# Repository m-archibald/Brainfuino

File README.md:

# Brainfuino [-]+.

```text
  ____            _        __       _           
 | __ ) _ __ __ _(_)_ __  / _|_   _(_)_ __   ___  
 |  _ \| '__/ _` | | '_ \| |_| | | | | '_ \ / _ \ 
 | |_) | | | (_| | | | | |  _| |_| | | | | | (_) |
 |____/|_|  \__,_|_|_| |_|_|  \__,_|_|_| |_|\___/ 
```

**An Arduino-like development board that executes raw Brainfuck natively in silicon.**

> ### 📖 [Read the Full Documentation](https://m-archibald.github.io/Brainfuino/)
>
> Comprehensive guides covering quick start, hardware architecture, FPGA toolchain, DirtyJTAG / Diamond flashing, STM32 firmware, 3D printing, and Brainfuck programming are live at **[https://m-archibald.github.io/Brainfuino/](https://m-archibald.github.io/Brainfuino/)**!

---

## What is Brainfuino?

You may have seen the Brainfuino [Hackaday project](https://hackaday.com/2021/01/12/make-room-for-a-new-arduino-competitor-with-native-brainfck/) released during COVID in 2021. Originally created by Eduardo Corpeño, it's a programming board that runs the esoteric programming language Brainfuck completely in hardware. The language is extremely minimal, with just 8 characters, yet it is entirely Turing complete. When uploading code to the Brainfuino, there is no conversion or compression, the ascii brainfuck characters are saved into rom exactly as they are written. Programming in Brainfuck is difficult, hilarious, and rewarding, and doing it with Brainfuino is even better.

---

## Two Processors: Pure Hardware and Quality of Life

There are two processors on the Brainfuino, the actual Brainfuck based soft processor implemented in hardware on the Lattice FPGA, and the STM32 which makes the whole thing user "friendly". Since the FPGA is configured basically as an old fashioned Harvard CPU, instructions move through the soft processor in a continuous stream of parallel bits, these flash into and out of existence, and the STM32 is there to catch them and serialize them so you can use it with a modern PC instead of an ancient parallel based terminal interface. The FPGA does all the hard work here though. When programs are run, all the output is being generated real time in hardware via the FPGA. The FPGA reads bytes of data from good old parallel flash program memory, and when it encounters bytes representing one of the 8 ascii characters used in Brainfuck it executes that with its built in soft processor based instruction set according to the character. Since it's a harvard style cpu, it also uses parallel based RAM to read and write data to and from for computation purposes. The STM32 uses its hardware timer to drive a clock pin to the FPGA at speeds from 500 khz up to 12 mhz. You may wonder if the STM32 is overkill, and your curiosity is valid, it probably is overkill, but by leveraging a separate microcontroller for these quality of life improvements, it allows the Brainfuck soft processor implemented in Verilog on the Lattice FPGA to remain pure and stay true to its purpose to compute Brainfuck. We leave the rest to the STM32: Usb communication, parallel to serial conversion, program memory flushing and prep, variable clock speed control, and an interactive terminal interface.

---

## Why Brainfuino?

As to answer the question of why? Well: The challenge. And to quote the original author Eduardo Corpeño, with the Brainfuino you get "bragging rights for writing code that works! You certainly won't get that from the Arduino."

---

## What's in Revision 1.1

My revision 1.1 of the Brainfuino has:
- Improved clock routing to the FPGA soft processor using an FPGA pin optimized for clock input rather than a generic GPIO
- Proper VBus to 3.3v connection on the STM32 increasing STM32 clock stability
- JLCPCB compatible parts list and reduced cost by switching to prestocked "basic" components.
- USB C!
- A nifty 3D printed case
- KiCAD design files (migrated from the original Autodesk Eagle)

See the original demo video: [Brainfuino: Hardware Brainfuck Processor (YouTube)](https://www.youtube.com/watch?v=QloNq8AoHvU)

---

## Three Languages in One Project

Three different programming paradigms come together to bring Brainfuino to life:

| Language        | Layer                    | Purpose                                                                                                                              |
| :-------------- | :----------------------- | :----------------------------------------------------------------------------------------------------------------------------------- |
| **Brainfuck**   | **Application**          | The end-user language. Programs are written in standard Brainfuck and run directly on the hardware tape.                             |
| **Verilog HDL** | **Processor Core**       | Defines the`brainfuck_uP` digital architecture, instruction decoder, and state machine synthesized into the FPGA bitstream (`.jed`). |
| **Embedded C**  | **Coprocessor Firmware** | Powers the STM32F072 microcontroller, managing USB CDC communications, clock synthesis, and ROM flashing.                            |

---

## Repository Structure

This repository is the consolidated monorepo for the entire Brainfuino project:

- [`brainfuino-PCB/`](./brainfuino-PCB/): Hardware schematics and board layouts for **Rev 1.0** (Eagle) and **Rev 1.1** (KiCad with JLCPCB fabrication Gerbers, BOM, and CPL).
- [`brainfuck_uP-FPGA-softprocessor/`](./brainfuck_uP-FPGA-softprocessor/): Lattice MachXO2 soft-processor in Verilog, pin constraints (`.lpf`), and Lattice Diamond project files.
- [`companion-STM32-firmware/`](./companion-STM32-firmware/): STM32F072 firmware (STM32CubeIDE project) handling USB CDC serial, clock generation, and ROM flashing.
- [`3D-printable-case/`](./3D-printable-case/): SolidWorks (`.SLDPRT`) and 3D printing CAD models (`.STEP`) for the custom enclosure.
- [`documentation/`](./documentation/): Comprehensive MkDocs Material documentation source files and project guides.

---

## Project Origins & Acknowledgements

The Brainfuino project was originally conceived, designed, and built by **Eduardo Corpeño** ([kuashio](https://github.com/kuashio)).

- **Video Demonstration:** [Brainfuino: Hardware Brainfuck Processor (YouTube)](https://youtu.be/QloNq8AoHvU)
- **Project Build Log:** [Brainfuino on Hackaday.io](https://hackaday.io/project/176757-brainfuino)
- **Original Soft-Processor:** [kuashio/brainfuck_uP](https://github.com/kuashio/brainfuck_up)
- **Original STM32 Firmware:** [kuashio/brainfuino-firmware](https://github.com/kuashio/brainfuino-firmware)
- **Brainfuck IDE:** [Visual brainfuck](https://sites.google.com/site/visualbf/)

Continued and maintained by:

- **Matthew Archibald:** Hardware modernization, KiCad Rev 1.1 redesign, JLCPCB manufacturing packages, 3D-printable case, and documentation.
- **Thalia Archibald:** Software architecture, compiler engineering, and curator of the [bfcorpus repository](https://github.com/thaliaarchi/bfcorpus) and [bfcoq](https://github.com/thaliaarchi/bfcoq).

---

### Ready to Build or Program?

Check out the official documentation for step-by-step assembly guides, bitstream flashing, and terminal operation:
**[https://m-archibald.github.io/Brainfuino/](https://m-archibald.github.io/Brainfuino/)**

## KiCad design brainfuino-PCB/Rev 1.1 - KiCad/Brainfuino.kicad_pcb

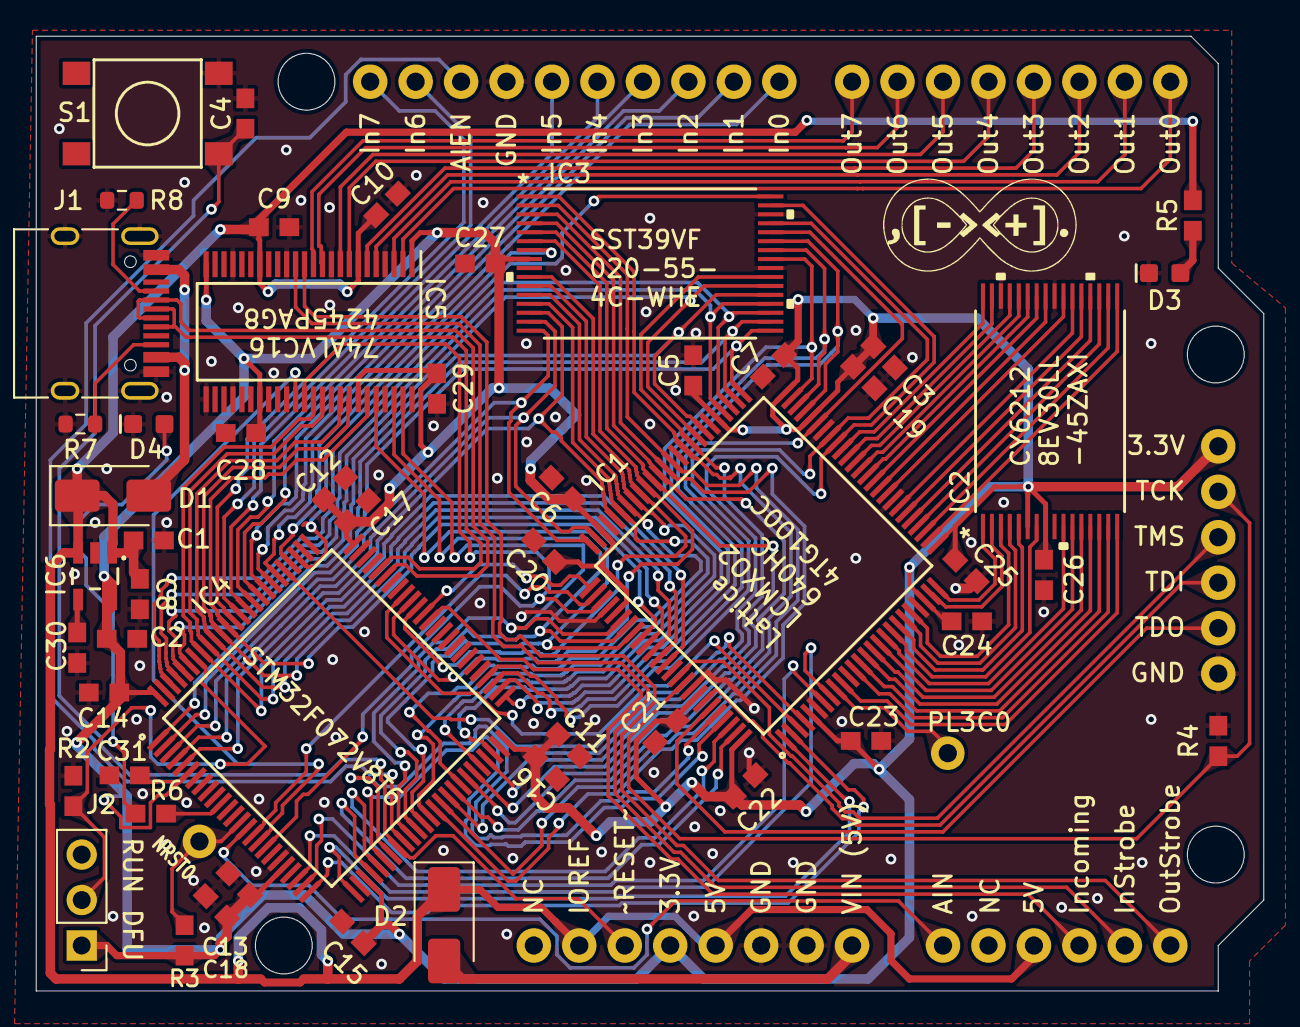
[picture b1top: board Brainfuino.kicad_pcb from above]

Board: 2 copper layers, 68.6 x 53.3 mm, 54 parts (0 on the bottom side), 119 nets.

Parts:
B1: ARDUINO_UNO_R3; ARDUINO_R3
C1: 10uF; 0603
C2, C8, C13: 1.0uF; 0603
C3, C4, C9, C10, C14, C15, C16, C17, C26, C27, C28, C29, C31: 0.1uF; 0603
C5, C6, C7, C18, C19, C20, C21, C22, C23, C24, C25, C30: 10nF; 0603
C11, C12: 4.7uF; 0603
D1, D2: SS12; D_SMA
D3: GREEN; LED-0603
D4: RED; LED-0603
IC1: LCMXO2-640HC-4TG100C; QFP50P1600X1600X160-100N
IC2: CY62128EV30LL-45AXI; TSOP-32
IC3: SST39LF020-55-4C-WHE; TSOP32_WH_SST
IC4: STM32F072V8T6; QFP50P1600X1600X160-100N
IC5: 74ALVC164245PAG8; SOP50P810X120-48N
IC6: SPX3819M5_3_3; SOT23-5
J1: USB_C_Receptacle_USB2.0_16P; USB_C_Receptacle_HRO_TYPE-C-31-M-12
J2: Conn_01x03_Pin; PinHeader_1x03_P2.54mm_Vertical
NRST0: TEST-POINTPOGO_PTH; 1X01_NO_SILK
PL3C0: TEST-POINTPOGO_PTH; 1X01_NO_SILK
R2: 22k; 0603
R3: 100k; 0603
R4, R5: 4.7k; 0603
R6: 680; 0603
R7, R8: 5.1k; R_0603_1608Metric
S1: RESET; TACTILE_SWITCH_SMD_6.2MM_TALL

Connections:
3.3V: B1.3.3V, B1.VCC, C2.1, C3.1, C5.1, C6.1, C7.1, C11.1, C12.1, C13.1, C14.1, C15.1, C16.1, C17.1, C18.1, C19.1, C20.1, C21.1, C22.1, C23.1, C24.1, C25.1, C26.1, C27.1, C28.1, C29.1, C31.2, IC1.5 (VCCIO3_1), IC1.23 (VCCIO3_2), IC1.26 (VCCIO2_1), IC1.46 (VCCIO2_2), IC1.50 (VCC_1), IC1.55 (VCCIO1_1), IC1.73 (VCCIO1_2), IC1.80 (VCCIO0_1), IC1.93 (VCCIO0_2), IC1.100 (VCC_2), IC2.6 (CE2), IC2.8 (VCC), IC3.8 (VDD), IC4.6 (VBAT), IC4.21 (VDDA), IC4.28 (VDD_1), IC4.50 (VDD_2), IC4.75 (VDDIO2), IC4.100 (VDD_3), IC5.1 (1DIR), IC5.24 (2DIR), IC5.31 (VCCA_(3.3V)_1), IC5.42 (VCCA_(3.3V)_2), IC6.5 (OUT), J2.1, R3.1
5V: B1.5V, B1.5V@1, B1.IOREF, C1.1, C8.1, C9.1, C10.1, D1.1 (K), D2.1 (K), IC5.7 ((5V)_VCCB_1), IC5.18 ((5V)_VCCB_2), IC6.1 (IN), IC6.3 (EN), R5.2
/A0: IC1.54 (PR7A), IC3.20 (A0), IC4.97 (PE0)
/A1: IC1.53 (PR7B), IC3.19 (A1), IC4.98 (PE1)
/A2: IC1.52 (PR7C), IC3.18 (A2), IC4.1 (PE2)
/A3: IC1.51 (PR7D), IC3.17 (A3), IC4.2 (PE3)
/A4: IC1.75 (PR2A), IC3.16 (A4), IC4.3 (PE4)
/A5: IC1.74 (PR2B), IC3.15 (A5), IC4.4 (PE5)
/A6: IC1.71 (PR2C), IC3.14 (A6), IC4.5 (PE6)
/A7: IC1.70 (PR2D), IC3.13 (A7), IC4.38 (PE7)
/A8: IC1.63 (PR5C), IC3.3 (A8), IC4.39 (PE8)
/A9: IC1.62 (PR5D), IC3.2 (A9), IC4.40 (PE9)
/A10: IC1.42 (PB12C), IC3.31 (A10), IC4.41 (PE10)
/A11: IC1.60 (PR6A), IC3.1 (A11), IC4.42 (PE11)
/A12: IC1.69 (PR3A), IC3.12 (A12), IC4.43 (PE12)
/A13: IC1.64 (PR5B), IC3.4 (A13), IC4.44 (PE13)
/A14: IC1.65 (PR5A), IC3.5 (A14), IC4.45 (PE14)
/A15: IC1.68 (PR3B), IC3.11 (A15), IC4.46 (PE15)
/A16: IC1.67 (PR3C), IC3.10 (A16), IC4.65 (PC8)
/A17: IC1.66 (PR3D), IC3.6 (A17), IC4.66 (PC9)
/AIEN: B1.AREF (AIEN), IC4.34 (PC5)
/AIN0: B1.AIN, IC4.15 (PC0)
/BF_CLK: IC1.3 (PL2C), IC4.67 (PA8)
/BF_RST: IC1.4 (PL2D), IC4.80 (PC12)
/BOOT0: IC4.94 (BOOT0), J2.2, R2.2
/BRD_RST: B1.RESET@1 (~RESET@1), C4.1, IC4.33 (PC4), S1.A2 (1)
/D0: IC1.57 (PR6D), IC3.21 (DQ0), IC4.95 (PB8)
/D1: IC1.58 (PR6C), IC3.22 (DQ1), IC4.96 (PB9)
/D2: IC1.59 (PR6B), IC3.23 (DQ2), IC4.47 (PB10)
/D3: IC1.49 (PB14D), IC3.25 (DQ3), IC4.48 (PB11)
/D4: IC1.48 (PB14C), IC3.26 (DQ4), IC4.51 (PB12)
/D5: IC1.47 (PB14B), IC3.27 (DQ5), IC4.52 (PB13)
/D6: IC1.45 (PB14A), IC3.28 (DQ6), IC4.53 (PB14)
/D7: IC1.43 (PB12D), IC3.29 (DQ7), IC4.54 (PB15)
/IN0: B1.IN0, IC4.81 (PD0)
/IN0_BFUP: IC1.8 (PL3B), IC4.23 (PA0)
/IN1: B1.IN1, IC4.82 (PD1)
/IN1_BFUP: IC1.7 (PL3A), IC4.24 (PA1)
/IN2: B1.IN2, IC4.83 (PD2)
/IN2_BFUP: IC1.2 (PL2B), IC4.25 (PA2)
/IN3: B1.IN3, IC4.84 (PD3)
/IN3_BFUP: IC1.1 (PL2A), IC4.26 (PA3)
/IN4: B1.IN4, IC4.85 (PD4)
/IN4_BFUP: IC1.99 (PT6A), IC4.29 (PA4)
/IN5: B1.IN5, IC4.86 (PD5)
/IN5_BFUP: IC1.98 (PT6B), IC4.30 (PA5)
/IN6: B1.IN6, IC4.87 (PD6)
/IN6_BFUP: IC1.97 (PT6C), IC4.31 (PA6)
/IN7: B1.IN7, IC4.88 (PD7)
/IN7_BFUP: IC1.96 (PT6D), IC4.32 (PA7)
/INCMG: B1.INCOMING, IC4.63 (PC6)
/INCMG_BFUP: IC1.76 (PT11D), IC4.64 (PC7)
/INSTRB: B1.INST (INSTRB), IC5.14 (2B2)
/INSTR_BFUP: IC1.77 (PT11C), IC4.16 (PC1)
/INSTR_LVL: IC4.17 (PC2), IC5.35 (2A2)
/OE: IC3.32 (~OE), IC4.78 (PC10)
/OUT0: IC1.81 (PT10D), IC4.35 (PB0), IC5.47 (1A1)
/OUT1: IC1.82 (PT10C), IC4.36 (PB1), IC5.46 (1A2)
/OUT2: IC1.83 (PT10B), IC4.37 (PB2), IC5.44 (1A3)
/OUT3: IC1.84 (PT10A), IC4.89 (PB3), IC5.43 (1A4)
/OUT4: IC1.85 (PT9D), IC4.90 (PB4), IC5.41 (1A5)
/OUT5: IC1.86 (PT9C), IC4.91 (PB5), IC5.40 (1A6)
/OUT6: IC1.87 (PT9B), IC4.92 (PB6), IC5.38 (1A7)
/OUT7: IC1.88 (PT9A), IC4.93 (PB7), IC5.37 (1A8)
/OUTSTRB: B1.OUTST (OUTSTRB), IC5.13 (2B1)
/OUTSTR_BFUP: IC1.78 (PT11A), IC4.18 (PC3), IC5.36 (2A1)
/TCK: B1.TCK, IC1.91 (PT7C), R4.2
/TDI: B1.TDI, IC1.94 (PT7B)
/TDO: B1.TDO, IC1.95 (PT7A)
/TMS: B1.TMS, IC1.90 (PT7D)
/USB_DN: IC4.70 (PA11), J1.A7 (D-), J1.B7 (D-)
/USB_DP: IC4.71 (PA12), J1.A6 (D+), J1.B6 (D+)
/WE: IC3.7 (~WE), IC4.79 (PC11)
GND: B1.GND@1 (GND), B1.GND@2 (GND@0), B1.GND@3 (GND@1), B1.GND@4 (GND@2), C1.2, C2.2, C3.2, C4.2, C5.2, C6.2, C7.2, C8.2, C9.2, C10.2, C11.2, C12.2, C13.2, C14.2, C15.2, C16.2, C17.2, C18.2, C19.2, C20.2, C21.2, C22.2, C23.2, C24.2, C25.2, C26.2, C27.2, C28.2, C29.2, C30.2, C31.1, D3.C, D4.C, IC1.6 (GND_1), IC1.22 (GND_2), IC1.33 (GND_3), IC1.44 (GND_4), IC1.56 (GND_5), IC1.72 (GND_6), IC1.79 (GND_7), IC1.92 (GND_8), IC2.24 (GND), IC2.30 (~CE1), IC3.24 (VSS), IC3.30 (~CE), IC4.20 (VSSA), IC4.27 (VSS_1), IC4.49 (VSS_2), IC4.74 (VSS_3), IC4.99 (VSS_4), IC5.4 (GND_1), IC5.10 (GND_2), IC5.15 (GND_3), IC5.21 (GND_4), IC5.25 (2~OE), IC5.28 (GND_5), IC5.34 (GND_6), IC5.39 (GND_7), IC5.45 (GND_8), IC5.48 (1~OE), IC6.2 (GND), J1.A1 (GND), J1.A12 (GND), J1.B1 (GND), J1.B12 (GND), J1.S1 (SHIELD), R2.1, R4.1, R7.2, R8.2, S1.B2 (2)
unnamed: D1.2 (A), J1.A4 (VBUS), J1.A9 (VBUS), J1.B4 (VBUS), J1.B9 (VBUS)
unnamed: B1.VIN, D2.2 (A)
unnamed: D3.A, R5.1
unnamed: D4.A, R6.1
unnamed: IC1.27 (PB4A), IC2.17 (A3)
unnamed: IC1.28 (PB4B), IC2.18 (A2)
unnamed: IC1.29 (PB4C), IC2.19 (A1)
unnamed: IC1.30 (PB4D), IC2.20 (A0)
unnamed: IC1.31 (PB6A), IC2.21 (I/O0)
unnamed: IC1.32 (PB6B), IC2.22 (I/O1)
unnamed: IC1.34 (PB6C), IC2.23 (I/O2)
unnamed: IC1.35 (PB6D), IC2.25 (I/O3)
unnamed: IC1.36 (PB10A), IC2.26 (I/O4)
unnamed: IC1.37 (PB10B), IC2.27 (I/O5)
unnamed: IC1.38 (PB10C), IC2.28 (I/O6)
unnamed: IC1.39 (PB10D), IC2.29 (I/O7)
unnamed: IC1.40 (PB12A), IC2.31 (A10)
unnamed: IC1.41 (PB12B), IC2.32 (~OE)
unnamed: IC1.9 (PL3C), PL3C0.1
unnamed: IC1.10 (PL3D), IC2.16 (A4)
unnamed: IC1.12 (PL5A), IC2.15 (A5)
unnamed: IC1.13 (PL5B), IC2.14 (A6)
unnamed: IC1.14 (PL5C), IC2.13 (A7)
unnamed: IC1.15 (PL5D), IC2.12 (A12)
unnamed: IC1.16 (PL6A), IC2.11 (A14)
unnamed: IC1.17 (PL6B), IC2.10 (A16)
unnamed: IC1.18 (PL6C), IC2.7 (A15)
unnamed: IC1.19 (PL6D), IC2.5 (~WE)
unnamed: IC1.20 (PL7A), IC2.4 (A13)
unnamed: IC1.21 (PL7B), IC2.3 (A8)
unnamed: IC1.24 (PL7C), IC2.2 (A9)
unnamed: IC1.25 (PL7D), IC2.1 (A11)
unnamed: IC4.14 (NRST), NRST0.1, R3.2
unnamed: IC4.11 (PF10), R6.2
unnamed: B1.OUT0, IC5.2 (1B1)
unnamed: B1.OUT1, IC5.3 (1B2)
unnamed: B1.OUT2, IC5.5 (1B3)
unnamed: B1.OUT3, IC5.6 (1B4)
unnamed: B1.OUT4, IC5.8 (1B5)
unnamed: B1.OUT5, IC5.9 (1B6)
unnamed: B1.OUT6, IC5.11 (1B7)
unnamed: B1.OUT7, IC5.12 (1B8)
unnamed: C30.1, IC6.4 (BP)
unnamed: J1.A5 (CC1), R8.1
unnamed: J1.B5 (CC2), R7.1

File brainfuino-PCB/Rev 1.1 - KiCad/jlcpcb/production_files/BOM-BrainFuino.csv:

Comment,Designator,Footprint,LCSC,Quantity
0.1uF,"C10,C14,C15,C16,C17,C26,C27,C28,C29,C3,C31,C4,C9",0603,C14663,13
1.0uF,"C13,C2,C8",0603,C15849,3
100k,R3,0603,C25803,1
10nF,"C18,C19,C20,C21,C22,C23,C24,C25,C30,C5,C6,C7",0603,C57112,12
10uF,C1,0603,C19702,1
22k,R2,0603,C31850,1
4.7k,"R4,R5",0603,C23162,2
4.7uF,"C11,C12",0603,C19666,2
5.1k,"R7,R8",R_0603_1608Metric,C23186,2
680,R6,0603,C23212,1
74ALVC164245PAG8,IC5,SOP50P810X120-48N,C2677360,1
CY62128EV30LL-45AXI,IC2,TSOP-32,C2944685,1
GREEN,D3,LED-0603,C2290,1
LCMXO2-640HC-4TG100C,IC1,QFP50P1600X1600X160-100N,C1519051,1
RED,D4,LED-0603,C2286,1
RESET,S1,TACTILE_SWITCH_SMD_6.2MM_TALL,C2909692,1
SPX3819M5_3_3,IC6,SOT23-5,C9055,1
SS12,"D1,D2",D_SMA,C2480,2
SST39LF020-55-4C-WHE,IC3,TSOP32_WH_SST,C630573,1
STM32F072V8T6,IC4,QFP50P1600X1600X160-100N,C125825,1
USB_C_Receptacle_USB2.0_16P,J1,USB_C_Receptacle_HRO_TYPE-C-31-M-12,C165948,1

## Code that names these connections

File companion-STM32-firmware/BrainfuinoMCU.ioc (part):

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Mcu.Name=STM32F072V(8-B)Tx
Mcu.Package=LQFP100
Mcu.UserName=STM32F072V8Tx
PA0.GPIOParameters=GPIO_Speed,PinState,GPIO_PuPd,GPIO_Label,GPIO_ModeDefaultOutputPP
PA0.GPIO_Label=BF_IN0
PA0.GPIO_ModeDefaultOutputPP=GPIO_MODE_OUTPUT_PP
PA0.GPIO_PuPd=GPIO_NOPULL
PA0.GPIO_Speed=GPIO_SPEED_FREQ_MEDIUM
PA0.PinState=GPIO_PIN_RESET
PA0.Signal=GPIO_Output
PA1.GPIOParameters=GPIO_Speed,PinState,GPIO_PuPd,GPIO_Label,GPIO_ModeDefaultOutputPP
PA1.GPIO_Label=BF_IN1
PA1.GPIO_ModeDefaultOutputPP=GPIO_MODE_OUTPUT_PP
PA1.GPIO_PuPd=GPIO_NOPULL
PA1.GPIO_Speed=GPIO_SPEED_FREQ_MEDIUM
PA1.PinState=GPIO_PIN_RESET
PA1.Signal=GPIO_Output
PA11.Mode=Device
PA11.Signal=USB_DM
PA12.Mode=Device
PA12.Signal=USB_DP
PA2.GPIOParameters=GPIO_Speed,PinState,GPIO_PuPd,GPIO_Label,GPIO_ModeDefaultOutputPP
PA2.GPIO_Label=BF_IN2
PA2.GPIO_ModeDefaultOutputPP=GPIO_MODE_OUTPUT_PP
PA2.GPIO_PuPd=GPIO_NOPULL
PA2.GPIO_Speed=GPIO_SPEED_FREQ_MEDIUM
PA2.PinState=GPIO_PIN_RESET
PA2.Signal=GPIO_Output
PA3.GPIOParameters=GPIO_Speed,GPIO_Label
PA3.GPIO_Label=BF_IN3
PA3.GPIO_Speed=GPIO_SPEED_FREQ_MEDIUM
PA3.Signal=GPIO_Output
PA4.GPIOParameters=GPIO_Speed,PinState,GPIO_PuPd,GPIO_Label,GPIO_ModeDefaultOutputPP
PA4.GPIO_Label=BF_IN4
PA4.GPIO_ModeDefaultOutputPP=GPIO_MODE_OUTPUT_PP
PA4.GPIO_PuPd=GPIO_NOPULL
PA4.GPIO_Speed=GPIO_SPEED_FREQ_MEDIUM
PA4.PinState=GPIO_PIN_RESET
PA4.Signal=GPIO_Output
PA5.GPIOParameters=GPIO_Speed,PinState,GPIO_PuPd,GPIO_Label,GPIO_ModeDefaultOutputPP
PA5.GPIO_Label=BF_IN5
PA5.GPIO_ModeDefaultOutputPP=GPIO_MODE_OUTPUT_PP
PA5.GPIO_PuPd=GPIO_NOPULL
PA5.GPIO_Speed=GPIO_SPEED_FREQ_MEDIUM
PA5.PinState=GPIO_PIN_RESET
PA5.Signal=GPIO_Output
PA6.GPIOParameters=GPIO_Speed,PinState,GPIO_PuPd,GPIO_Label,GPIO_ModeDefaultOutputPP
PA6.GPIO_Label=BF_IN6
PA6.GPIO_ModeDefaultOutputPP=GPIO_MODE_OUTPUT_PP
PA6.GPIO_PuPd=GPIO_NOPULL
PA6.GPIO_Speed=GPIO_SPEED_FREQ_MEDIUM
PA6.PinState=GPIO_PIN_RESET
PA6.Signal=GPIO_Output
PA7.GPIOParameters=GPIO_Speed,PinState,GPIO_PuPd,GPIO_Label,GPIO_ModeDefaultOutputPP
PA7.GPIO_Label=BF_IN7
PA7.GPIO_ModeDefaultOutputPP=GPIO_MODE_OUTPUT_PP
PA7.GPIO_PuPd=GPIO_NOPULL
PA7.GPIO_Speed=GPIO_SPEED_FREQ_MEDIUM
PA7.PinState=GPIO_PIN_RESET
PA7.Signal=GPIO_Output
PA8.GPIOParameters=GPIO_Speed,GPIO_Label
PA8.GPIO_Label=BF_CLK
PA8.GPIO_Speed=GPIO_SPEED_FREQ_HIGH
PA8.Mode=Clock-out
PA8.Signal=RCC_MCO
PB0.GPIOParameters=GPIO_Label
PB0.GPIO_Label=BF_OUT0
PB0.Signal=GPIO_Input
PB1.GPIOParameters=GPIO_Label
PB1.GPIO_Label=BF_OUT1
PB1.Signal=GPIO_Input
PB10.GPIOParameters=GPIO_Label
PB10.GPIO_Label=D2
PB10.Signal=GPIO_Input
PB11.GPIOParameters=GPIO_Label
PB11.GPIO_Label=D3
PB11.Signal=GPIO_Input
PB12.GPIOParameters=GPIO_Label
PB12.GPIO_Label=D4
PB12.Signal=GPIO_Input
PB13.GPIOParameters=GPIO_Label
PB13.GPIO_Label=D5
PB13.Signal=GPIO_Input
PB14.GPIOParameters=GPIO_Label
PB14.GPIO_Label=D6
PB14.Signal=GPIO_Input
PB15.GPIOParameters=GPIO_Label
PB15.GPIO_Label=D7
PB15.Signal=GPIO_Input
PB2.GPIOParameters=GPIO_Label
PB2.GPIO_Label=BF_OUT2
PB2.Signal=GPIO_Input
PB3.GPIOParameters=GPIO_Label
PB3.GPIO_Label=BF_OUT3
PB3.Signal=GPIO_Input
PB4.GPIOParameters=GPIO_Label
PB4.GPIO_Label=BF_OUT4
PB4.Signal=GPIO_Input
PB5.GPIOParameters=GPIO_Label
PB5.GPIO_Label=BF_OUT5
PB5.Signal=GPIO_Input
PB6.GPIOParameters=GPIO_Label
PB6.GPIO_Label=BF_OUT6
PB6.Signal=GPIO_Input
PB7.GPIOParameters=GPIO_Label
PB7.GPIO_Label=BF_OUT7
PB7.Signal=GPIO_Input
PB8.GPIOParameters=GPIO_Label
PB8.GPIO_Label=D0
PB8.Signal=GPIO_Input
PB9.GPIOParameters=GPIO_Label
PB9.GPIO_Label=D1
PB9.Signal=GPIO_Input
PC0.GPIOParameters=GPIO_Label
PC0.GPIO_Label=AIN0
PC0.Mode=IN10
PC0.Signal=ADC_IN10
PC1.GPIOParameters=GPIO_PuPd,GPIO_Label,GPIO_ModeDefaultEXTI
PC1.GPIO_Label=BF_INSTRB
PC1.GPIO_ModeDefaultEXTI=GPIO_MODE_IT_FALLING
PC1.GPIO_PuPd=GPIO_PULLUP
PC1.Signal=GPXTI1
PC10.GPIOParameters=GPIO_Speed,PinState,GPIO_Label
PC10.GPIO_Label=OE
PC10.GPIO_Speed=GPIO_SPEED_FREQ_MEDIUM
PC10.PinState=GPIO_PIN_SET
PC10.Signal=GPIO_Output
PC11.GPIOParameters=GPIO_Speed,PinState,GPIO_Label
PC11.GPIO_Label=WE
PC11.GPIO_Speed=GPIO_SPEED_FREQ_MEDIUM
PC11.PinState=GPIO_PIN_SET
PC11.Signal=GPIO_Output
PC12.GPIOParameters=GPIO_Label
PC12.GPIO_Label=BF_RST
PC12.Signal=GPIO_Output
PC2.GPIOParameters=GPIO_Speed,PinState,GPIO_Label
PC2.GPIO_Label=BRD_INSTRB
PC2.GPIO_Speed=GPIO_SPEED_FREQ_HIGH
PC2.PinState=GPIO_PIN_SET
PC2.Signal=GPIO_Output
PC3.GPIOParameters=GPIO_Label
PC3.GPIO_Label=BF_OUTSTRB
PC3.Signal=GPXTI3
PC4.GPIOParameters=GPIO_PuPd,GPIO_Label
PC4.GPIO_Label=BRD_RST
PC4.GPIO_PuPd=GPIO_PULLUP
PC4.Signal=GPIO_Input
PC5.GPIOParameters=GPIO_PuPd,GPIO_Label
PC5.GPIO_Label=AIEN
PC5.GPIO_PuPd=GPIO_PULLDOWN
PC5.Signal=GPIO_Input
PC6.GPIOParameters=GPIO_PuPd,GPIO_Label
PC6.GPIO_Label=BRD_INCMG
PC6.GPIO_PuPd=GPIO_PULLDOWN
PC6.Signal=GPIO_Input
PC7.GPIOParameters=GPIO_Label
PC7.GPIO_Label=BF_INCMG
PC7.Signal=GPIO_Output
PC8.GPIOParameters=GPIO_Label
PC8.GPIO_Label=A16
PC8.Signal=GPIO_Input
PC9.GPIOParameters=GPIO_Label
PC9.GPIO_Label=A17
PC9.Signal=GPIO_Input
PD0.GPIOParameters=GPIO_Label
PD0.GPIO_Label=IN0
PD0.Signal=GPIO_Input
PD1.GPIOParameters=GPIO_Label
PD1.GPIO_Label=IN1
PD1.Signal=GPIO_Input
PD2.GPIOParameters=GPIO_Label
PD2.GPIO_Label=IN2
PD2.Signal=GPIO_Input
PD3.GPIOParameters=GPIO_Label
PD3.GPIO_Label=IN3
PD3.Signal=GPIO_Input
PD4.GPIOParameters=GPIO_Label
PD4.GPIO_Label=IN4
PD4.Signal=GPIO_Input
PD5.GPIOParameters=GPIO_Label
PD5.GPIO_Label=IN5
PD5.Signal=GPIO_Input
PD6.GPIOParameters=GPIO_Label
PD6.GPIO_Label=IN6
PD6.Signal=GPIO_Input
PD7.GPIOParameters=GPIO_Label
PD7.GPIO_Label=IN7
PD7.Signal=GPIO_Input
PE0.GPIOParameters=GPIO_Label
PE0.GPIO_Label=A0
PE0.Signal=GPIO_Input
PE1.GPIOParameters=GPIO_Label
PE1.GPIO_Label=A1
PE1.Signal=GPIO_Input
PE10.GPIOParameters=GPIO_Label
PE10.GPIO_Label=A10
PE10.Signal=GPIO_Input
PE11.GPIOParameters=GPIO_Label
PE11.GPIO_Label=A11
PE11.Signal=GPIO_Input
PE12.GPIOParameters=GPIO_Label
PE12.GPIO_Label=A12
PE12.Signal=GPIO_Input
PE13.GPIOParameters=GPIO_Label
PE13.GPIO_Label=A13
PE13.Signal=GPIO_Input
PE14.GPIOParameters=GPIO_Label
PE14.GPIO_Label=A14
PE14.Signal=GPIO_Input
PE15.GPIOParameters=GPIO_Label
PE15.GPIO_Label=A15
PE15.Signal=GPIO_Input
PE2.GPIOParameters=GPIO_Label
PE2.GPIO_Label=A2
PE2.Signal=GPIO_Input
PE3.GPIOParameters=GPIO_Label
PE3.GPIO_Label=A3
PE3.Signal=GPIO_Input
PE4.GPIOParameters=GPIO_Label
PE4.GPIO_Label=A4
PE4.Signal=GPIO_Input
PE5.GPIOParameters=GPIO_Label
PE5.GPIO_Label=A5
PE5.Signal=GPIO_Input
PE6.GPIOParameters=GPIO_Label
PE6.GPIO_Label=A6
PE6.Signal=GPIO_Input
PE7.GPIOParameters=GPIO_Label
PE7.GPIO_Label=A7
PE7.Signal=GPIO_Input
PE8.GPIOParameters=GPIO_Label
PE8.GPIO_Label=A8
PE8.Signal=GPIO_Input
PE9.GPIOParameters=GPIO_Label
PE9.GPIO_Label=A9
PE9.Signal=GPIO_Input
PF10.GPIOParameters=PinState,GPIO_Label
PF10.GPIO_Label=LED
PF10.PinState=GPIO_PIN_RESET
PF10.Signal=GPIO_Output
RCC.SYSCLKFreq_VALUE=48000000
RCC.SYSCLKSource=RCC_SYSCLKSOURCE_HSI48
board=custom

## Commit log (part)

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2026-02-07 added notes on features to add
2026-02-23 Enhance roadmap with checkboxes and completed tasks
    Updated the roadmap section with checkboxes for potential features and marked one feature as completed.
